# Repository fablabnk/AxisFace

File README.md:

https://www.home-wrecker.com/sili-face2.html

Pavlos' version is here: https://github.com/Sysex89/fuzzface

# Components / BOM

2 transistors, 4 resistors, 3 caps and 2 pots

# Description of the circuit

I tried to summarise the key points of the deep-dive into the fuzz-face found [here](https://www.electrosmash.com/fuzz-face).

`The circuit is a simple 2 stage amplifier with a feedback network path. It can be broken down into three parts: Input Stage, Output Stage and Feedback Network. The last block (the Feedback Network) will affect the rest of the analysis because it will influence the most important parameters: voltage gain, input impedance, output impedance and frequency response.`

## Input Stage:

- Input jack
- 2.2uF capacitor:  blocks any DC level, removing hum and protecting the pedal/guitar against dangerous DC levels
- AC128 transistor:
- 33K resistor: sets the main input stage parameters like the voltage gain, bias points, and maximum collector current

## Output Stage:

PNP Common Emitter Amplifier
variable emitter degeneration resistor (RFUZZ=1KΩ)

The output stage of the Fuzz Face circuit boosts the signal to drive the amplifier and enhances harmonic content, resulting in a distinctive, saturated fuzz effect.

Input Capacitor (C2): Blocks DC voltage while allowing AC signal to pass through.
Emitter Resistor (RE): Sets the bias point and stabilizes the transistor.
Emitter Bypass Capacitor (CE): Increases gain and frequency response.
Output Capacitor (C3): Blocks DC voltage while allowing AC signal to pass through, shaping the output frequency response.
Volume Potentiometer (RV1): Adjusts the level of the output signal

## Feedback Network:

- When the fuzz control (1KΩ pot) is set to minimum, a big amount of signal is sent back to the input, creating a big feedback loop and reducing the total pedal gain (left image below).

When the fuzz control increases the attack, the 20uF C2 cap will gradually shunt the negative feedback to the ground, thus letting the circuit operate with more gain (right image below).

# Expected behaviour of the circuit

# Transistor types

Is is important to decide first if we will use NPN or PNP transisors in our design, as this affects the overall topology of the schematic. I decided to use the 2N3906 PNP transistor, as we have a transistor kit similar to [this](https://www.amazon.com/BOJACK-General-Purpose-Transistors-Assortment/dp/B07T61SY9Y/ref=sr_1_2_sspa?crid=3CZ8I2M8Y477&dib=eyJ2IjoiMSJ9.K72wwbAF5iW2kf8H6Fox1LnOYMAHnPOKU5US_5vlfMn8DHxB5zyEE168C56UF1AWR4pkUgDK8s8D_Qz6BV7tvaUW_ADToqoFVJ2cdKOUBkSo3u3PCN5OYQ6I2IzFou0xQqVvCv1qnfxc-Z7mjKhpS5aYe4Fm7NDoV1I8iaLPPa_7kdqWA5mqpBDd1apUEIc43sA2lfgUod4YT-uKydM7tf_C24xex0AyWmWGq5bC2kc.DDjJLIM_iIoefxprtJl_gLEOM4SSovt4RaqQyJyAWJw&dib_tag=se&keywords=transistor+kit&qid=1716450756&sprefix=transistor+ki%2Caps%2C179&sr=8-2-spons&sp_csd=d2lkZ2V0TmFtZT1zcF9hdGY&psc=1) in our lab. We should be able to easily switch them out later if we don't like the sound.

- BC108 NPN Silicon transistor (Pavlos' version)
- AC128 PNP Geranium transistor (simulatable version, see below)

In an NPN transistor, the layers are arranged as N-type semiconductor sandwiched between two layers of P-type semiconductor.
In a PNP transistor, the layers are arranged as P-type semiconductor sandwiched between two layers of N-type semiconductor.
This difference leads to opposite polarities of voltage and current flow between the emitter, base, and collector terminals for NPN and PNP transistors.

There is also a lot of mythology around geranium transistors - which are favored in guitar pedals for their warm, vintage tone, soft clipping distortion, dynamic response, and historical significance. ideal for us would be to use silicon transistors we have in our lab, 

# Simulation

https://forum.kicad.info/t/fuzz-face-tone-bender-projects-updated-05-22-23/41450

PNP

## Simulating Potentiometers

The 

I would 

Q: Is there a way to plot multiple potentiometer values side by side?

## Another approach: tuning

# Potentiometer values

We don't have 100

# Footswitch

- A range of footswitch wiring methods are described [here](https://stinkfoot.se/archives/2233)
- We will use the "better true bypass" method, as we want to make ususe the DPDT footswitches we already have in stock
- We will try to include the bypass wiring as part of the wiring of our main PCB, but if the layout doesn't make sense, we could design a mini bypass PCB
- In future we prefer to use a 3PDT, so as to also have an LED that shows when the fuzz is on or off

# Power

9V Battery

# Audio Ins/Outs

Q: How do they mount?

# PCB Layout

Q: What case will we use?
A: A recycled metal tin

# JLCPCB Plugin

# Misc

Lots of other circuit resources: https://electronotes.netfirms.com/free.htm

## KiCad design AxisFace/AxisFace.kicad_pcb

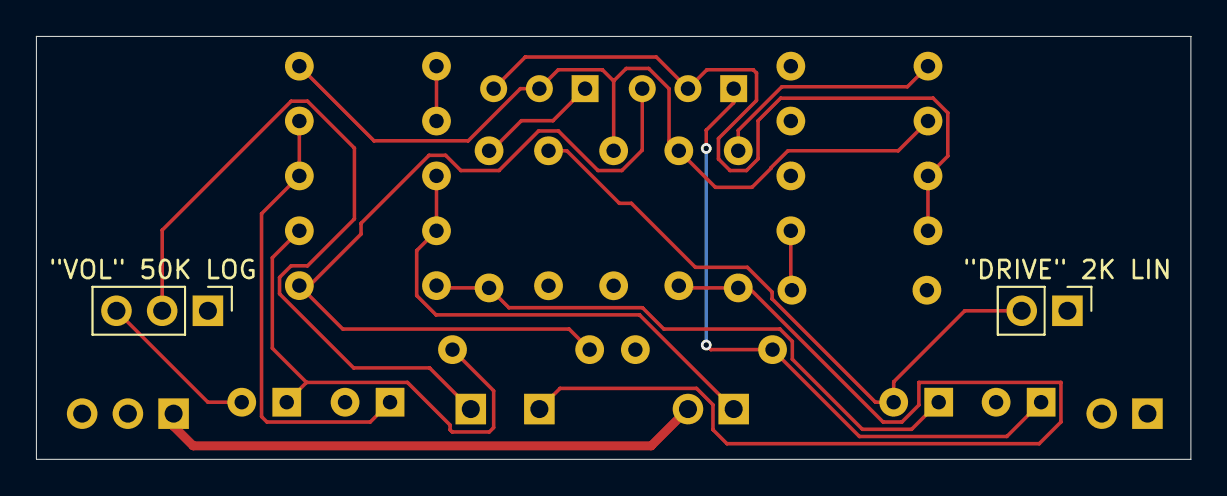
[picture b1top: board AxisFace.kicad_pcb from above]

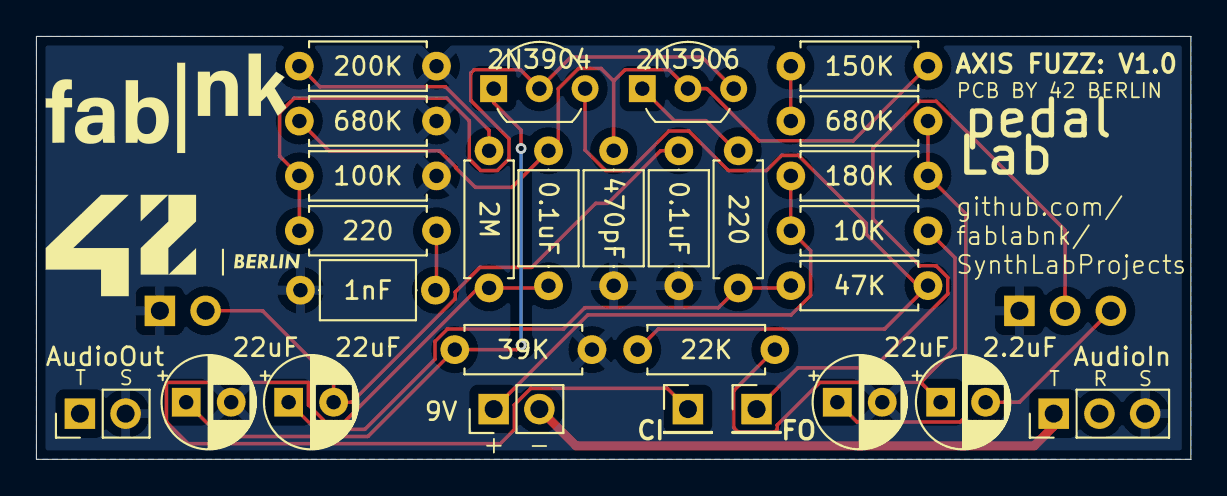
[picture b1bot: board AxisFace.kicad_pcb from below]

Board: 2 copper layers, 64.1 x 23.5 mm, 30 parts (28 on the bottom side), 18 nets.

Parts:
"DRIVE" 2K LIN: 2K lin DRIVE; PinHeader_1x02_P2.54mm_Vertical
"VOL" 50K LOG: 50K log VOL; PinHeader_1x03_P2.54mm_Vertical
C1: 2.2uF; CP_Radial_D5.0mm_P2.50mm
C2, C3, C7: 22uF; CP_Radial_D5.0mm_P2.50mm
C4: 1nF; C_Axial_L5.1mm_D3.1mm_P7.50mm_Horizontal
C5, C8: 0.1uF; C_Axial_L5.1mm_D3.1mm_P7.50mm_Horizontal
C6: 470pF; C_Axial_L5.1mm_D3.1mm_P7.50mm_Horizontal
J2: FX Return; PinHeader_1x01_P2.54mm_Vertical
J3: From FX Send; PinHeader_1x01_P2.54mm_Vertical
J10: AudioIn; PinHeader_1x03_P2.54mm_Vertical_TRS
J12: AudioOut; PinHeader_1x02_P2.54mm_Vertical_TS
Q1: 2N3904; TO-92_Inline_Wide
Q2: 2N3906; TO-92_Inline_Wide
R1: 22K; R_Axial_DIN0207_L6.3mm_D2.5mm_P7.62mm_Horizontal
R2: 180K; R_Axial_DIN0207_L6.3mm_D2.5mm_P7.62mm_Horizontal
R3: 10K; R_Axial_DIN0207_L6.3mm_D2.5mm_P7.62mm_Horizontal
R4, R10: 680K; R_Axial_DIN0207_L6.3mm_D2.5mm_P7.62mm_Horizontal
R5, R11: 220; R_Axial_DIN0207_L6.3mm_D2.5mm_P7.62mm_Horizontal
R6: 100K; R_Axial_DIN0207_L6.3mm_D2.5mm_P7.62mm_Horizontal
R7: 150K; R_Axial_DIN0207_L6.3mm_D2.5mm_P7.62mm_Horizontal
R8: 39K; R_Axial_DIN0207_L6.3mm_D2.5mm_P7.62mm_Horizontal
R9: 2M; R_Axial_DIN0207_L6.3mm_D2.5mm_P7.62mm_Horizontal
R12: 47K; R_Axial_DIN0207_L6.3mm_D2.5mm_P7.62mm_Horizontal
R13: 200K; R_Axial_DIN0207_L6.3mm_D2.5mm_P7.62mm_Horizontal
V1: 9V; PinHeader_1x02_P2.54mm_Vertical

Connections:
-9V: J10.T, V1.2
GND: "DRIVE" 2K LIN.1, "VOL" 50K LOG.1, C2.2, C3.2, C4.2, C6.2, C8.2, J10.S, J12.S, R6.1, R8.1, R10.1, R13.1
unnamed: C1.1, R1.1, R3.2
unnamed: "VOL" 50K LOG.3, C1.2
unnamed: C2.1, R2.1, R4.2
unnamed: C4.1, R5.2
unnamed: C7.1, R11.1, R12.2
unnamed: "DRIVE" 2K LIN.2, C7.2, C8.1
unnamed: "VOL" 50K LOG.2, J2.1
unnamed: C5.1, J3.1, R9.2
unnamed: Q1.2 (B), Q2.3 (C), R5.1, R6.2
unnamed: Q1.3 (C), R1.2, R12.1
unnamed: C3.1, Q1.1 (E), R8.2
unnamed: C5.2, C6.1, Q2.2 (B), R7.1, R10.2
unnamed: Q2.1 (E), R11.2
unnamed: R2.2, R3.1, V1.1
unnamed: R4.1, R7.2
unnamed: R9.1, R13.2

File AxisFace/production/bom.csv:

Designator,Footprint,Quantity,Value,LCSC Part #
"""DRIVE"" 2K LIN",PinHeader_1x02_P2.54mm_Vertical,1,2K lin DRIVE,
"""VOL"" 50K LOG",PinHeader_1x03_P2.54mm_Vertical,1,50K log VOL,
C1,CP_Radial_D5.0mm_P2.50mm,1,2.2uF,
"C2, C3, C7",CP_Radial_D5.0mm_P2.50mm,3,22uF,
C4,C_Axial_L5.1mm_D3.1mm_P7.50mm_Horizontal,1,1nF,
"C5, C8",C_Axial_L5.1mm_D3.1mm_P7.50mm_Horizontal,2,0.1uF,
C6,C_Axial_L5.1mm_D3.1mm_P7.50mm_Horizontal,1,470pF,
J10,PinHeader_1x03_P2.54mm_Vertical_TRS,1,AudioIn,
J12,PinHeader_1x02_P2.54mm_Vertical_TS,1,AudioOut,
J2,PinHeader_1x01_P2.54mm_Vertical,1,FX Return,
J3,PinHeader_1x01_P2.54mm_Vertical,1,From FX Send,
Q1,TO-92_Inline_Wide,1,2N3904,
Q2,TO-92_Inline_Wide,1,2N3906,
R1,R_Axial_DIN0207_L6.3mm_D2.5mm_P7.62mm_Horizontal,1,22K,
"R10, R4",R_Axial_DIN0207_L6.3mm_D2.5mm_P7.62mm_Horizontal,2,680K,
"R11, R5",R_Axial_DIN0207_L6.3mm_D2.5mm_P7.62mm_Horizontal,2,220,
R12,R_Axial_DIN0207_L6.3mm_D2.5mm_P7.62mm_Horizontal,1,47K,
R13,R_Axial_DIN0207_L6.3mm_D2.5mm_P7.62mm_Horizontal,1,200K,
R2,R_Axial_DIN0207_L6.3mm_D2.5mm_P7.62mm_Horizontal,1,180K,
R3,R_Axial_DIN0207_L6.3mm_D2.5mm_P7.62mm_Horizontal,1,10K,
R6,R_Axial_DIN0207_L6.3mm_D2.5mm_P7.62mm_Horizontal,1,100K,
R7,R_Axial_DIN0207_L6.3mm_D2.5mm_P7.62mm_Horizontal,1,150K,
R8,R_Axial_DIN0207_L6.3mm_D2.5mm_P7.62mm_Horizontal,1,39K,
R9,R_Axial_DIN0207_L6.3mm_D2.5mm_P7.62mm_Horizontal,1,2M,
V1,PinHeader_1x02_P2.54mm_Vertical,1,9V,

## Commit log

2024-06-08 ready for production
2024-06-15 pcb now meets custom design rules for jlcpcb
2024-07-02 moved README and notes into KiCad folder
